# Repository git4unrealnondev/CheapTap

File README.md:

# Cheaptap PCB

A mod to make tap more afforable / easier to use.

 BOM

 SMD

1: 34-30v ~500ma SOD-123 zener
1: 0603 330nf cap 50v rated
1: L78L05_SOT89
1: 0603 100nf
1: 0603 200R
1: 0603 640R
1: 0603 RED LED

 THT

1: ITR9608
1: 3P 2.00MM HORIZONTAL FEMALE CONNECTOR

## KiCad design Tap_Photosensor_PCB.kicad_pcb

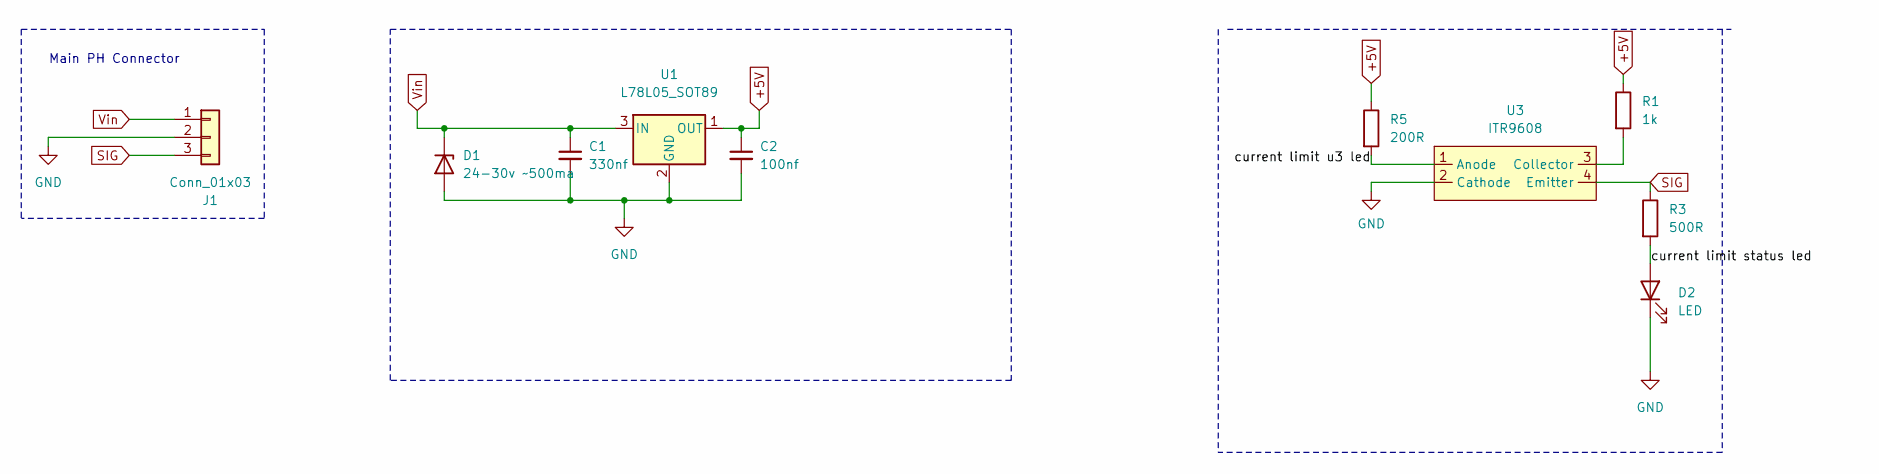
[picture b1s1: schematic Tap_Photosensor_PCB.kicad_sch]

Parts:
C1: 330nf; C_0603_1608Metric
C2: 100nf; C_0603_1608Metric
D1: 24-30v ~500ma; D_SOD-123
D2: LED; LED_0603_1608Metric
J1: Conn_01x03; JST_PH_S3B-PH-K_1x03_P2.00mm_Horizontal
R1: 1k; R_0603_1608Metric
R3: 500R; R_0603_1608Metric
R5: 200R; R_0603_1608Metric
U1: L78L05_SOT89; SOT-89-3
U3: ITR9608; itr9608r

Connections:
+5V: C2.1, R1.1, R5.1, U1.1 (OUT)
/current limit status led: D2.2 (A), R3.2
/current limit u3 led: R5.2, U3.1 (Anode)
GND: C1.2, C2.2, D1.2 (A), D2.1 (K), J1.2, U1.2 (GND), U3.2 (Cathode)
unnamed: R1.2, U3.3 (Collector)
SIG: J1.3, R3.1, U3.4 (Emitter)
Vin: C1.1, D1.1 (K), J1.1, U1.3 (IN)

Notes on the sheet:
Main PH Connector

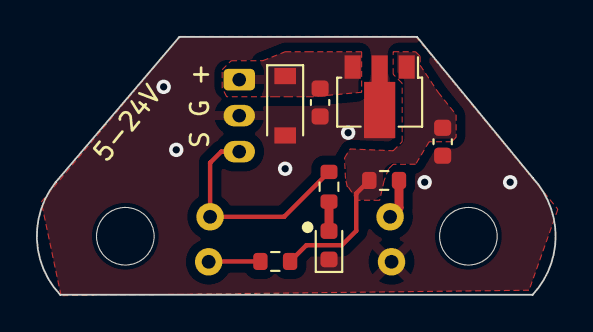
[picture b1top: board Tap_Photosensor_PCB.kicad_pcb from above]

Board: 2 copper layers, 28.8 x 14.3 mm, 10 parts (0 on the bottom side), 7 nets.

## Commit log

2023-01-30 Init
2023-01-30 Adding gerbers
2025-12-27 Adding panelization and R3
2025-12-27 fixing mistake
2025-12-27 updating panel
